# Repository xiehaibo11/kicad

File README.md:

# Kicad：AI 终端、VS Code 扩展与 KiCad 自动化

本项目在 KiCad 开源 EDA 软件基础上，增加 **Kicad AI 终端、Kicad VS Code 扩展和
共享 JavaScript 原生工具**。可以用自然语言描述工程、原理图和 PCB 任务，由 AI 按需求调用
KiCad 工具，并查看执行记录、检查结果和需要用户决定的问题。

AI 工具的完整源码和构建文档位于
[`codex/kicad-npm` 分支](https://github.com/xiehaibo11/kicad/tree/codex/kicad-npm)。
默认分支首页同步展示本说明；下面的 AI 工具链接均指向该开发分支。

## 我们的工具

| 工具 | 用途 | 源码与文档 |
|---|---|---|
| **Kicad 终端** | 基于完整 OpenCode 运行时的 CLI/TUI，保留模型、认证、插件、会话、工具、服务端 API、Web 界面和原有子命令，直接调用共享 JavaScript 原生工具。 | [终端](https://github.com/xiehaibo11/kicad/tree/codex/kicad-npm/tools/ai/Kicad-terminal) · [npm 安装说明](https://github.com/xiehaibo11/kicad/blob/codex/kicad-npm/tools/ai/Kicad-terminal/npm/README.md) |
| **Kicad（VS Code）** | 基于 Claudix 的聊天扩展，提供模型与推理强度选择、权限模式、提示词优化、下一句建议、子代理运行看板和可展开的执行记录。 | [扩展](https://github.com/xiehaibo11/kicad/tree/codex/kicad-npm/tools/ai/Kicad-extension) |
| **共享 JS 工具** | 终端和扩展在进程内调用同一份 JavaScript，直接使用 KiCad 原生 IPC/CLI。 | [后端](https://github.com/xiehaibo11/kicad/tree/codex/kicad-npm/tools/ai/direct) · [工具集说明](https://github.com/xiehaibo11/kicad/blob/codex/kicad-npm/tools/ai/README.md) |

## 安装 Kicad 终端

本次完整更新为 **GitHub 0.1.1 / 扩展 0.4.23**。npm 官方 `latest` 目前仍为 0.1.0，
0.1.1 等待 npm 账号的发布双重认证配置；[发布状态](https://github.com/xiehaibo11/kicad/blob/codex/kicad-npm/tools/ai/releases/2026-10-engineering/npm-publication-status.json)
有明确记录。立即使用 0.1.1 可运行：

```sh
npx --yes --package=https://github.com/xiehaibo11/kicad/releases/download/kicad-code-v0.1.1/-kicadai-kicad-code-0.1.1.tgz Kicad
```

直接下载并启动完整终端：

```sh
npx --yes @-kicadai/kicad-code@latest
```

或者全局安装，以后使用软件名称启动：

```sh
npm install -g @-kicadai/kicad-code@latest
Kicad
```

启动名称支持全部大小写组合，包括 `Kicad`、`kicad`、`KICAD` 和 `KiCad`。
继续已有会话使用 `Kicad --continue`，查看命令使用 `Kicad --help`。

当前 npm 包支持 **macOS Apple Silicon（arm64）、Node.js 22 及以上版本**，随包分发完整
原生终端运行时、共享 JavaScript 工具、技能和插件。首次使用模型需要对应服务商认证；已有模型配置
和会话继续沿用。操作实际设计需要另行安装 KiCad；定制 API 功能需要本仓库相应源码构建的
KiCad 支持。

[npm 公开包](https://www.npmjs.com/package/@-kicadai/kicad-code) ·
[发行包与验收报告](https://github.com/xiehaibo11/kicad/releases/tag/kicad-code-v0.1.1)

## 在 VS Code 中使用

扩展面板显示名称为 **Kicad**，终端入口显示为 **Kicad 终端**，扩展 ID 为 `kicad-agent.kicad`。
从 [GitHub Release 下载扩展 0.4.23](https://github.com/xiehaibo11/kicad/releases/tag/kicad-extension-v0.4.23)
中的 `kicad-0.4.23.vsix`，在 VS Code 扩展菜单选择 **从 VSIX 安装…**，或者在下载目录执行：

```sh
code --install-extension ./kicad-0.4.23.vsix --force
```

需要 VS Code 1.98 或以上版本；当前验证平台为 macOS Apple Silicon。VSIX 包含聊天界面和
SDK/CLI，KiCad 软件、原生 CLI 及完整终端运行时需要单独安装，共享 JavaScript 工具随包提供。依赖、构建和安装步骤见
[扩展文档](https://github.com/xiehaibo11/kicad/blob/codex/kicad-npm/tools/ai/Kicad-extension/README.md)
和 [AI 工具集说明](https://github.com/xiehaibo11/kicad/blob/codex/kicad-npm/tools/ai/README.md)。

- 直接发送自然语言任务，按需求调用工具；新对话默认展示 Agent，用户选择的模型持续沿用。
- 推理强度通过输入框 UI 选择；终端通过 `/effort` 选择当前模型支持的档位。
- 魔杖使用当前选择的模型优化输入框文字，可撤销，不自动发送；下一句建议按 Tab 接受到草稿。
- 模型实际启动子代理后显示运行看板入口；工具执行过程默认折叠，点击查看详情。
- 支持暂停、编辑原消息后重新发送，继续沿用会话中的模型、推理强度和权限选择。

## KiCad 工具调用与设计检查

终端和扩展共用后端工具及任务规则，覆盖以下操作入口：

- 工程发现与切换、文档打开、原理图和 PCB 信息读取。
- 元件与封装库查询、原理图生成、放置、扇出、布线与制造文件导出。
- DRC/ERC、连通性、DFM 和结构检查；具体设计检查在后端执行。
- 按任务自动查询 20 个主题、86 条工程规则与 37 个 KiCad 原版示例索引；按工程快照校验证据完整性。
- 公开网页资料搜索与读取，通过 `kicad_web` 等后端工具按任务调用。

当前发布包的能力目录包含 **20 组 KiCad 内部工具、254 个类型化动作**，详细清单由
`node tools/ai/direct/dist/kicad-direct.mjs manifest` 输出。工具目录、原生动作索引和实际执行验证是不同层次；
IPC 动作是否可用取决于当前 KiCad 版本、编辑器和已注册的接口处理器。当前仍有部分 PCB
接口适配问题，某些会话会返回 `UNHANDLED`；工程和板级接口需要逐项验证。
设计结果以文档回读、DRC/ERC 及相应检查报告为准。

## 获取源码与构建

```sh
git clone --branch codex/kicad-npm https://github.com/xiehaibo11/kicad.git Kicad
cd Kicad
git submodule update --init --recursive
```

| 路径 | 内容 |
|---|---|
| [`tools/ai/Kicad-terminal`](https://github.com/xiehaibo11/kicad/tree/codex/kicad-npm/tools/ai/Kicad-terminal) | 终端品牌适配、构建与安装脚本 |
| [`tools/ai/Kicad-terminal/npm`](https://github.com/xiehaibo11/kicad/tree/codex/kicad-npm/tools/ai/Kicad-terminal/npm) | npm 包入口、打包与安装验收 |
| [`tools/ai/Kicad-extension`](https://github.com/xiehaibo11/kicad/tree/codex/kicad-npm/tools/ai/Kicad-extension) | VS Code 聊天扩展适配与构建 |
| [`tools/ai/direct`](https://github.com/xiehaibo11/kicad/tree/codex/kicad-npm/tools/ai/direct) | KiCad 自动化、MCP、IPC、CLI 和后端检查 |
| [`tools/ai/composer`](https://github.com/xiehaibo11/kicad/tree/codex/kicad-npm/tools/ai/composer) | 终端与扩展共用的交互逻辑和任务规则 |

完整依赖和构建命令见
[AI 工具集文档](https://github.com/xiehaibo11/kicad/blob/codex/kicad-npm/tools/ai/README.md)。

## 开源来源与许可证

本项目为独立维护的 KiCad 二次开发，集成和适配了
[KiCad](https://gitlab.com/kicad/code/kicad)、
[OpenCode](https://github.com/anomalyco/opencode)、
[Claudix](https://github.com/Haleclipse/Claudix) 和
[easyeda-agent](https://github.com/zhoushoujianwork/easyeda-agent)。各组件保留原有版权、许可证和
来源记录，具体见仓库 [LICENSE](LICENSE)、各组件目录及 npm 包的
[第三方声明](https://github.com/xiehaibo11/kicad/blob/codex/kicad-npm/tools/ai/Kicad-terminal/npm/THIRD_PARTY_NOTICES.md)。

---

## KiCad 上游开发文档

For specific documentation about [building KiCad](https://dev-docs.kicad.org/en/build/), policies
and guidelines, and source code documentation see the
[Developer Documentation](https://dev-docs.kicad.org) website.

You may also take a look into the [Wiki](https://gitlab.com/kicad/code/kicad/-/wikis/home),
the [contribution guide](https://dev-docs.kicad.org/en/contribute/).

For general information about KiCad and information about contributing to the documentation and
libraries, see our [Website](https://kicad.org/) and our [Forum](https://forum.kicad.info/).

## Build state

KiCad uses a host of CI resources.

GitLab CI pipeline status can be viewed for Linux and Windows builds of the latest commits.

## Release status

## Files
* [AUTHORS.txt](AUTHORS.txt) - The authors, contributors, document writers and translators list
* [CMakeLists.txt](CMakeLists.txt) - Main CMAKE build tool script
* [copyright.h](copyright.h) - A very short copy of the GNU General Public License to be included in new source files
* [Doxyfile](Doxyfile) - Doxygen config file for KiCad
* [INSTALL.txt](INSTALL.txt) - The release (binary) installation instructions
* [uncrustify.cfg](uncrustify.cfg) - Uncrustify config file for uncrustify sources formatting tool
* [_clang-format](_clang-format) - clang config file for clang-format sources formatting tool

## Subdirectories

* [3d-viewer](3d-viewer)         - Sourcecode of the 3D viewer
* [bitmap2component](bitmap2component)  - Sourcecode of the bitmap to PCB artwork converter
* [cmake](cmake)      - Modules for the CMAKE build tool
* [common](common)            - Sourcecode of the common library
* [cvpcb](cvpcb)             - Sourcecode of the CvPCB tool
* [demos](demos)             - Some demo examples
* [doxygen](doxygen)     - Configuration for generating pretty doxygen manual of the codebase
* [eeschema](eeschema)          - Sourcecode of the schematic editor
* [gerbview](gerbview)          - Sourcecode of the gerber viewer
* [include](include)           - Interfaces to the common library
* [kicad](kicad)             - Sourcecode of the project manager
* [libs](libs)           - Sourcecode of KiCad utilities (geometry and others)
* [pagelayout_editor](pagelayout_editor) - Sourcecode of the pagelayout editor
* [patches](patches)           - Collection of patches for external dependencies
* [pcbnew](pcbnew)           - Sourcecode of the printed circuit board editor
* [plugins](plugins)           - Sourcecode for the 3D viewer plugins
* [qa](qa)                - Unit testing framework for KiCad
* [resources](resources)         - Packaging resources such as bitmaps and operating system specific files
    - [bitmaps_png](resources/bitmaps_png)       - Menu and program icons
    - [project_template](resources/project_template)          - Project template
* [thirdparty](thirdparty)           - Sourcecode of external libraries used in KiCad but not written by the KiCad team
* [tools](tools)             - Helpers for developing, testing and building
* [translation](translation) - Translation data files (managed through [Weblate](https://hosted.weblate.org/projects/kicad/master-source/) for most languages)
* [utils](utils)             - Small utils for KiCad, e.g. IDF, STEP, and OGL tools and converters

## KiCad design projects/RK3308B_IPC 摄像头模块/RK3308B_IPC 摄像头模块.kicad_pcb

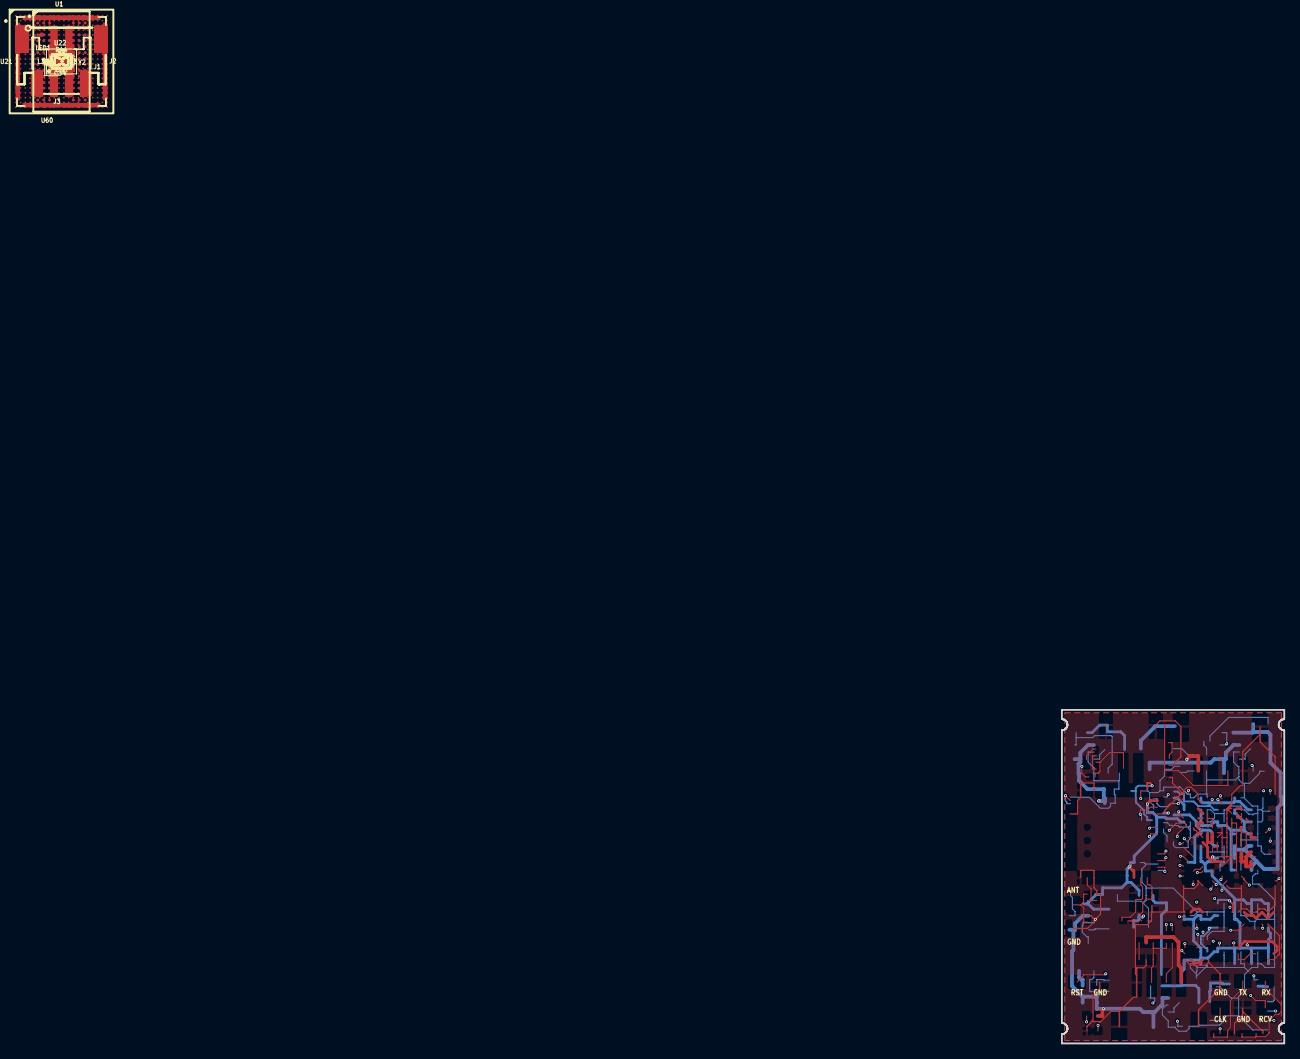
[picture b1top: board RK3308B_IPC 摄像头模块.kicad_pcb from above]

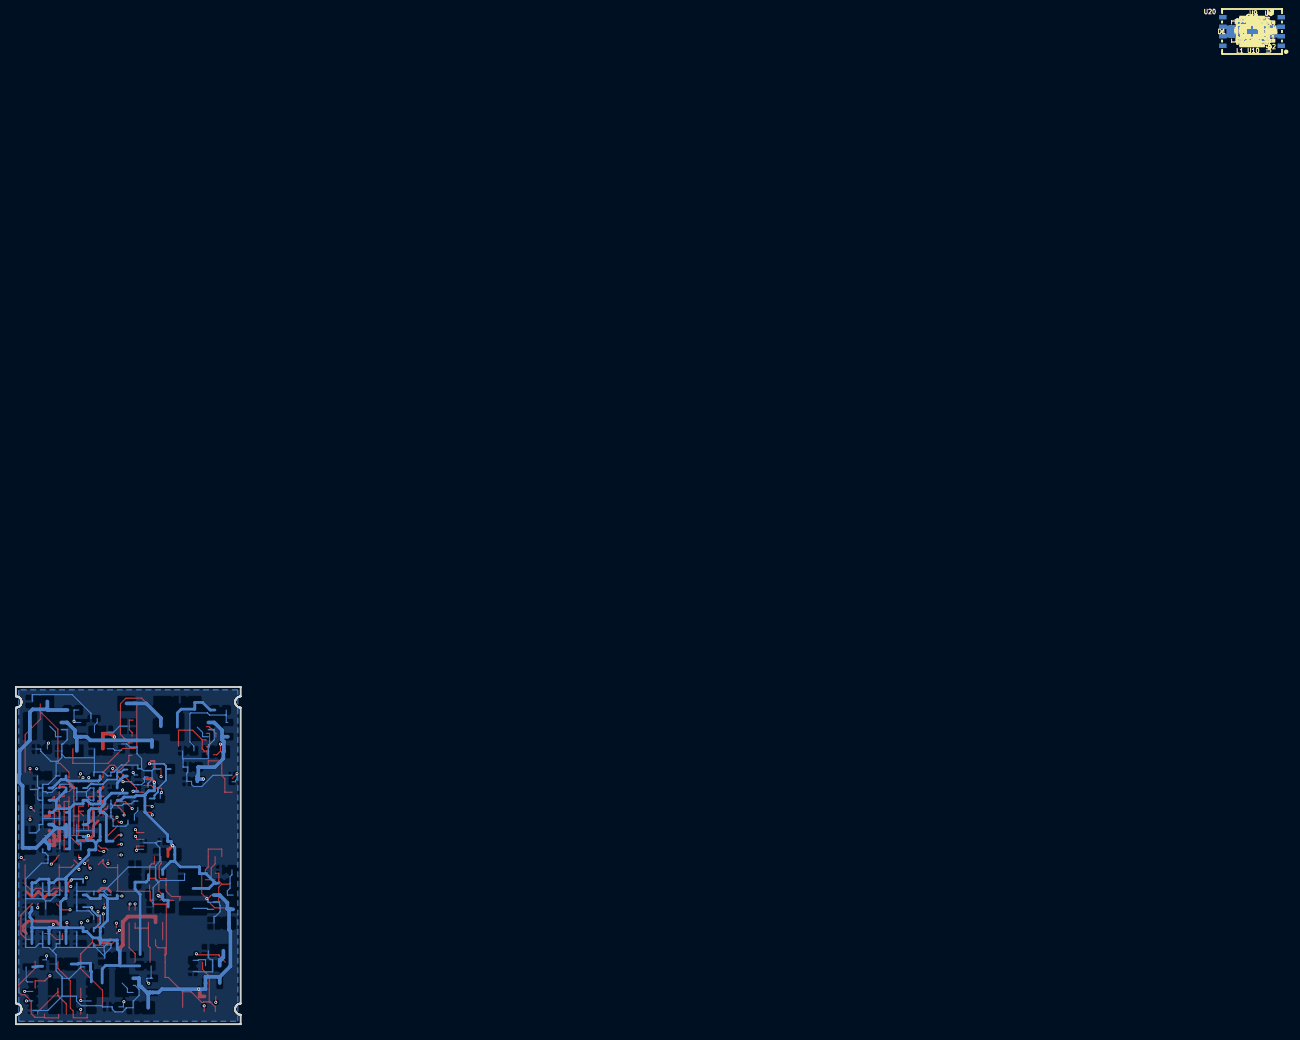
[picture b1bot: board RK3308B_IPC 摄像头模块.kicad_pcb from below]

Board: 4 copper layers, 30.0 x 45.0 mm, 155 parts (117 on the bottom side), 125 nets.

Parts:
C1, C3, C5, C7, C9, C10: CAPCER10UF25VX5R0805; C0805
C2, C4, C6, C8, C12, C13: 22uF-C0805_L; C0805
C11, C14: 100nF/0603/50V; C0603
C20, C31, C32, C40, C52, C61, C62, C63, C64, C66, C67, C69, C70, C71, C72, C73, C74, C75, C76, C77, C78, C79, C80, C81, C82, C84, C85, C86, C87, C101, C102, C103, C104, C105, C106, C107, C108, C109, C110, C111, C112, C113, C114, C115, C116, C117, C118, C122, C123: 100nF; C0402
C21, C30: 10uF; C0805
C33: 2.2uF; C0603
C34, C35: 1pF; C0402
C36, C37, C50, C51: 12pF; C0402
C41, C83, C119, C120: 1uF; C0402
C53: 1nF; C0402
C60, C65, C68, C121: 22uF; C0805
C89, C90: 4.7uF; C0603
D1: SS34; SMA_L4.3-W2.6-LS5.0-RD
D2: SMAJ5.0A; SMA_L4.4-W2.6-LS5.0-RD
D3, D4, D5, D6, D7, D8: ESD9B5.0ST5G; SOD-923_L0.8-W0.6-LS1.0-BI
J1: S2B-PH-SM4-TB(LF)(SN); CONN-SMD_P2.00_S2B-PH-SM4-TB-LF-SN
J2, J3: S4B-PH-SM4-TB(LF)(SN); CONN-SMD_S4B-PH-SM4-TB-LF-SN
L1, L2, L3, L4: 2.2uH; IND-SMD_L3.0-W3.0
L30: 4.7uH; L0603
L31: DLW21HN900SQ2L; FILTER-SMD_4P-L2.0-W1.3-BL_DLW21
LED1: LED-0603R; LED0603-RD_RED
R1: 15kΩ; R0603
R2, R6: 20kΩ; R0603
R3: 6.81kΩ; R0603
R4, R10: 10kΩ; R0603
R5: 24.9kΩ; R0603
R7: 100kΩ; R0603
R8: 22.1kΩ; R0603
R9: 1kΩ; R0603
R20, R21, R22, R30, R31, R40, R50, R52: 10kΩ; R0402
R32: 0Ω; R0402
R41: 18kΩ; R0402
R42, R43, R44, R45, R46: 100Ω; R0402
R51: 133Ω; R0402
R53, R54: 1Ω; R0402
R101, R102: 1kΩ; R0402
R103: 240Ω; R0402
TP30, TP31, TP32, TP33, TP34, TP35, TP36, TP37, TP38, TP39: RCU-0C; TESTPOINT-SMD_L1.6-W0.8_RCU-0C
U1: RK3308B; BGA-355_L13.0-W13.0-P0.65_RK3308
U5, U6, U7, U8: SY8089AAAC; SOT-23-5_L3.0-W1.7-P0.95-LS2.8-BR
U9: AP2112K-1.8TRG1; SOT-25_L3.0-W1.6-P0.95-LS2.8-BL
U10: SY6280AAC; SOT-23-5_L3.0-W1.7-P0.95-LS2.8-BL
U20: W25N02KVZEIR; WSON-8_L8.0-W6.0-P1.27-TL-EP-1
U21: 2.4GHz; QFN-44_L12.0-W12.0-P0.90-TL_AP6212
U22: USBLC6-2SC6; SOT-23-6_L2.9-W1.6-P0.95-LS2.8-BL
U60: K4B4G1646E-BYMA; FBGA-96_L13.5-W7.5-R16-C6-P0.80-TL
Y1: 24MHz; CRYSTAL-SMD_4P-L3.2-W2.5-BL
Y2: 26MHz; CRYSTAL-SMD_4P-L3.2-W2.5-BL

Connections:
$4N75: C35.1, R32.2, TP30.1
+1V8: C10.1, C81.1, C82.1, C83.1, C84.1, R50.1, R54.1, U1.D17, U1.E16, U1.M17, U1.N17, U9.5
+3V3: C8.1, C9.1, C20.1, C21.1, C30.1, C31.1, C32.1, C72.1, C73.1, C74.1, C75.1, C76.1, C77.1, C78.1, C79.1, C80.1, L4.1, R7.2, R20.1, R21.1, R22.1, U1.D13, U1.D14, U1.E14, U1.J14, U1.N5, U1.P16, U1.R11, U1.R12, U1.T11, U9.1, U9.3, U20.8, U21.9, U21.22
+5V: C1.1, C3.1, C5.1, C7.1, C11.1, C13.1, C14.1, D1.1, R9.2, U5.1, U5.4, U6.1, U6.4, U7.1, U7.4, U8.1, U8.4, U10.4, U10.5
+5V_CAM: C12.1, J3.4, R40.1, U10.1, U22.5
+5V_IN: D1.2, D2.1, J2.4
ANT_MOD: C34.1, R32.1, U21.2
AOUT: C41.1, U1.W20
AOUT_C: C41.2, D6.2, J1.2
AVCM: C89.1, U1.R18
AVCMH: C90.1, U1.T18
BT_HOST_WAKE: U1.R4, U21.7
BT_REG_ON: R31.1, U1.F19, U21.34
BT_UART_CTS: U1.K19, U21.41
BT_UART_RTS: U1.K18, U21.44
BT_UART_RX: U1.F17, U21.42
BT_UART_TX: U1.J16, U21.43
BT_WAKE: U1.G16, U21.6
DBG_RX: R46.2, U1.B15
DBG_RX_C: D8.1, R46.1, TP33.1
DBG_TX: R45.2, U1.A15
DBG_TX_C: D7.1, R45.1, TP32.1
DDR_A0: U1.B4, U60.N3
DDR_A1: U1.A5, U60.P7
DDR_A2: U1.A3, U60.P3
DDR_A3: U1.E6, U60.N2
DDR_A4: U1.B7, U60.P8
DDR_A5: U1.B3, U60.P2
DDR_A6: U1.A6, U60.R8
DDR_A7: U1.A2, U60.R2
DDR_A8: U1.A10, U60.T8
DDR_A9: U1.E7, U60.R3
DDR_A10: U1.C9, U60.L7
DDR_A11: U1.B5, U60.R7
DDR_A12: U1.B6, U60.N7
DDR_A13: U1.D7, U60.T3
DDR_A14: U1.B10, U60.T7
DDR_BA0: U1.B2, U60.M2
DDR_BA1: U1.C8, U60.N8
DDR_BA2: U1.D6, U60.M3
DDR_CASN: U1.D8, U60.K3
DDR_CKE: U1.B9, U60.K9
DDR_CLK: U1.C3, U60.J7
DDR_CLKN: U1.C2, U60.K7
DDR_CS0N: U1.B1, U60.L2
DDR_DM0: U1.G1, U60.E7
DDR_DM1: U1.L3, U60.D3
DDR_DQ0: U1.J4, U60.E3
DDR_DQ1: U1.G5, U60.F7
DDR_DQ2: U1.H4, U60.F2
DDR_DQ3: U1.L1, U60.F8
DDR_DQ4: U1.E2, U60.H3
DDR_DQ5: U1.F1, U60.H8
DDR_DQ6: U1.E3, U60.G2
DDR_DQ7: U1.K2, U60.H7
DDR_DQ8: U1.F4, U60.D7
DDR_DQ9: U1.G2, U60.C3
DDR_DQ10: U1.L4, U60.C8
DDR_DQ11: U1.D3, U60.C2
DDR_DQ12: U1.L2, U60.A7
DDR_DQ13: U1.F3, U60.A2
DDR_DQ14: U1.M2, U60.B8
DDR_DQ15: U1.K5, U60.A3
DDR_DQS0: U1.J3, U60.F3
DDR_DQS0N: U1.K4, U60.G3
DDR_DQS1: U1.H2, U60.C7
DDR_DQS1N: U1.H3, U60.B7
DDR_ODT0: U1.C5, U60.K1
DDR_RASN: U1.D5, U60.J3
DDR_RESET: U1.E4, U60.T2
DDR_WEN: U1.E8, U60.L3
DDR_ZQ: R103.1, U60.L8
FB_3V3: R7.1, R8.1, U8.5
FB_CORE: R1.1, R2.1, U5.5
FB_DDR: R5.1, R6.1, U7.5
FB_LOG: R3.1, R4.1, U6.5
FLASH_SEL: R52.1, U1.R3
GND: C1.2, C2.2, C3.2, C4.2, C5.2, C6.2, C7.2, C8.2, C9.2, C10.2, C11.2, C12.2, C13.2, C14.2, C20.2, C21.2, C30.2, C31.2, C32.2, C33.2, C34.2, C35.2, C36.2, C37.2, C40.2, C50.2, C51.2, C52.2, C53.2, C60.2, C61.2, C62.2, C63.2, C64.2, C65.2, C66.2, C67.2, C68.2, C69.2, C70.2, C71.2, C72.2, C73.2, C74.2, C75.2, C76.2, C77.2, C78.2, C79.2, C80.2, C81.2, C82.2, C83.2, C84.2, C85.2, C86.2, C87.2, C89.2, C90.2, C101.2, C102.2, C103.2, C104.2, C105.2, C106.2, C107.2, C108.2, C109.2, C110.2, C111.2, C112.2, C113.2, C114.2, C115.2, C116.2, C117.2, C118.2, C119.2, C120.2, C121.2, C122.2, C123.2, D2.2, D3.1, D4.1, D5.1, D6.1, D7.2, D8.2, J1.3, J1.4, J2.1, J2.5, J2.6, J3.1, J3.5, J3.6, LED1.1, R2.2, R4.2, R6.2, R8.2, R10.1, R30.2, R31.2, R41.2, R51.2, R52.2, R102.2, R103.2, TP31.1, TP34.1, TP36.1, TP38.1, U1.A1, U1.A4, U1.A9, U1.A20, U1.B8, U1.B11, U1.C4, U1.C6, U1.C7, U1.C11, U1.C13, U1.C17, U1.D2, U1.D11, U1.D12, U1.D19, U1.D20, U1.E1, U1.E5, U1.E9, U1.E11, U1.E12, U1.E13, U1.E18, U1.F2, U1.F13, U1.F14, U1.F15, U1.F16, U1.G3, U1.G8, U1.G9, U1.G13, U1.G14, U1.G15, U1.H7, U1.H8, U1.H9, U1.H10, U1.H11, U1.H12, U1.H13, U1.H17, U1.J5, U1.J7, U1.J8, U1.J9, U1.J10, U1.J11, U1.J12, U1.J13, U1.K1, U1.K3, U1.K7, U1.K8, U1.K9, U1.K10, U1.K11, U1.K12, U1.K13, U1.K14, U1.K15, U1.K16, U1.K17, U1.L5, U1.L7, U1.L8, U1.L9, U1.L10, U1.L11, U1.L12, U1.L13, U1.L14, U1.L15, U1.L16, U1.L17, U1.L18, U1.L19, U1.L20, U1.M4, U1.M5, U1.M6, U1.M7, U1.M8, U1.M9, U1.M10, U1.M11, U1.M12, U1.M13, U1.M14, U1.M15, U1.M16, U1.N1, U1.N9, U1.N10, U1.N11, U1.N12, U1.N13, U1.N14, U1.N15, U1.N16, U1.P8, U1.P9, U1.P10, U1.P11, U1.P12, U1.P13, U1.P14, U1.P15, U1.R7, U1.R14, U1.R17, U1.T7, U1.U17, U1.Y1, U1.Y20, U5.2, U6.2, U7.2, U8.2, U9.2, U10.2, U20.4, U20.9, U21.1, U21.3, U21.20, U21.31, U21.33, U21.36, U22.2, U60.A9, U60.B1, U60.B3, U60.B9, U60.D1, U60.D8, U60.E1, U60.E2, U60.E8, U60.F9, U60.G1, U60.G8, U60.G9, U60.J2, U60.J8, U60.M1, U60.M9, U60.P1, U60.P9, U60.T1, U60.T9, Y1.2, Y1.4, Y2.2, Y2.4
IRCUTA: R44.1, U1.T5
IRCUTA_C: D5.2, J1.1, R44.2
ISET_CAM: R10.2, U10.3
J2_IO1: R42.1, U1.V3
J2_IO1_C: D3.2, J2.3, R42.2
J2_IO2: R43.1, U1.W2
J2_IO2_C: D4.2, J2.2, R43.2
LED_PWR: LED1.2, R9.1
RECOVERY: C53.1, R50.2, TP35.1, U1.A19
RESET_N: C52.1, TP39.1, U1.B20
SDIO_CLK: U1.J18, U21.17
SDIO_CMD: U1.H18, U21.16
SDIO_D0: U1.J19, U21.18
SDIO_D1: U1.J17, U21.19
SDIO_D2: U1.G18, U21.14
SDIO_D3: U1.G17, U21.15
SPI_CLK: TP37.1, U1.W11, U20.6
SPI_CS0: R20.2, U1.V11, U20.1
SPI_IO2: R21.2, U1.Y12, U20.3
SPI_IO3: R22.2, U1.Y11, U20.7
SPI_MISO: U1.V12, U20.2
SPI_MOSI: U1.U11, U20.5
SW_3V3: L4.2, U8.3
SW_CORE: L1.2, U5.3
SW_DDR: L3.2, U7.3
SW_LOG: L2.2, U6.3
USB_CON_DM: J3.3, L31.1, U22.1, U22.6
USB_CON_DP: J3.2, L31.4, U22.3, U22.4
USB_DET: C40.1, R40.2, R41.1, U1.C14
USB_DM: L31.2, U1.A13
USB_DP: L31.3, U1.B13
USB_EXTR: R51.1, U1.C15
V1P0_USB: C87.1, R53.2, U1.D15, U1.E15
V1P8_ANA: C85.1, C86.1, R54.2, U1.D16, U1.E17
VDD_CORE: C2.1, C60.1, C61.1, C62.1, C63.1, C64.1, L1.1, R1.2, U1.N6, U1.N7, U1.N8, U1.P5, U1.P6, U1.P7, U1.R5, U1.R6, U1.R8
VDD_DDR: C6.1, C68.1, C69.1, C70.1, C71.1, C101.1, C102.1, C103.1, C104.1, C105.1, C106.1, C107.1, C108.1, C109.1, C110.1, C111.1, C112.1, C113.1, C114.1, C115.1, C116.1, C117.1, C118.1, C119.1, C120.1, C121.1, L3.1, R5.2, R101.1, U1.E10, U1.F7, U1.F8, U1.F9, U1.G6, U1.H6, U1.J6, U60.A1, U60.A8, U60.B2, U60.C1, U60.C9, U60.D2, U60.D9, U60.E9, U60.F1, U60.G7, U60.H2, U60.H9, U60.K2, U60.K8, U60.N1, U60.N9, U60.R1, U60.R9
VDD_LOG: C4.1, C65.1, C66.1, C67.1, L2.1, R3.2, R53.1, U1.F10, U1.F11, U1.F12, U1.G10, U1.G11, U1.G12
VREF_DDR: C122.1, C123.1, R101.2, R102.1, U60.H1, U60.M8
WIFI_32K: U1.Y2, U21.24
WIFI_REG_ON: R30.1, U1.P3, U21.12
WIFI_WAKE_HOST: U1.N3, U21.13
WL_BUCK_LX: L30.1, U21.21
WL_VIN_LDO: C33.1, L30.2, U21.23
WL_XTAL_IN: C36.1, U21.10, Y2.1
WL_XTAL_OUT: C37.1, U21.11, Y2.3
XIN_24M: C50.1, U1.E19, Y1.1
XOUT_24M: C51.1, U1.E20, Y1.3
